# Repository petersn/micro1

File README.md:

## Dependencies:

```
pip install cocotb
sudo apt-get install iverilog
```

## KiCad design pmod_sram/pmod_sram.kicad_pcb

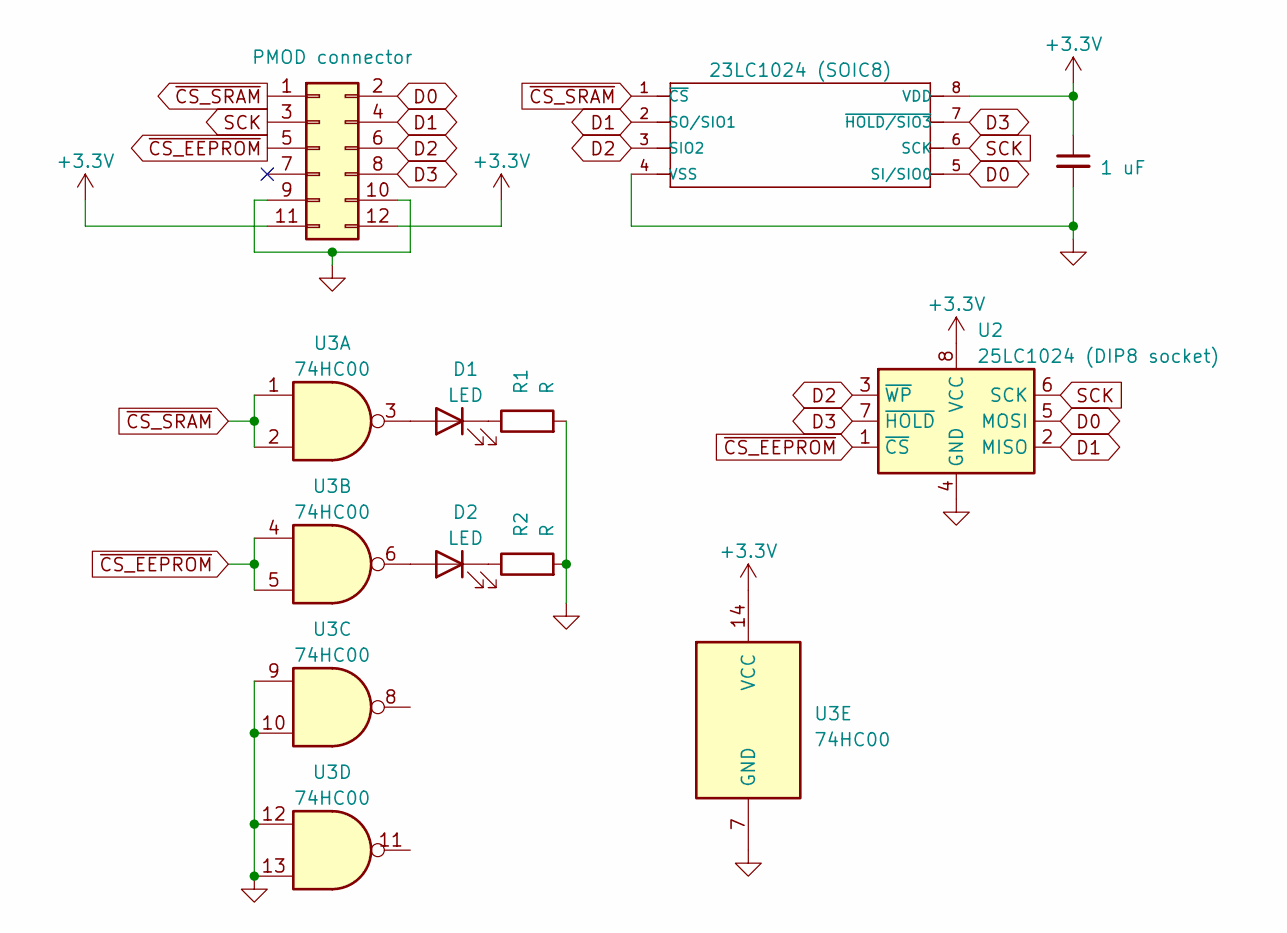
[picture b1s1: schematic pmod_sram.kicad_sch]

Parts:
C1: 1 uF; C_0603_1608Metric_Pad1.08x0.95mm_HandSolder
D1, D2: LED; LED_0603_1608Metric_Pad1.05x0.95mm_HandSolder
J1: PMOD connector; PinHeader_2x06_P2.54mm_Vertical
R1, R2: R; R_0603_1608Metric_Pad0.98x0.95mm_HandSolder
U1: 23LC1024 (SOIC8); SOIC-8_3.9x4.9mm_P1.27mm; MPN 23LC1024T-E/ST
U2: 25LC1024 (DIP8 socket); DIP-8_W7.62mm
U3: 74HC00; SOIC-14_3.9x8.7mm_P1.27mm

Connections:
+3.3V: C1.1, J1.11, J1.12, U1.8 (VDD), U2.8 (VCC), U3.14 (VCC)
D0: J1.2, U1.5 (SI/SIO0), U2.5 (MOSI)
D1: J1.4, U1.2 (SO/SIO1), U2.2 (MISO)
D2: J1.6, U1.3 (SIO2), U2.3 (~WP)
D3: J1.8, U1.7 (~HOLD/SIO3), U2.7 (~HOLD)
GND: C1.2, J1.9, J1.10, R1.2, R2.2, U1.4 (VSS), U2.4 (GND), U3.7 (GND), U3.9, U3.10, U3.12, U3.13
unnamed: D1.2 (A), U3.3
unnamed: D1.1 (K), R1.1
unnamed: D2.2 (A), U3.6
unnamed: D2.1 (K), R2.1
SCK: J1.3, U1.6 (SCK), U2.6 (SCK)
~CS_EEPROM: J1.5, U2.1 (~CS), U3.4, U3.5
~CS_SRAM: J1.1, U1.1 (~CS), U3.1, U3.2

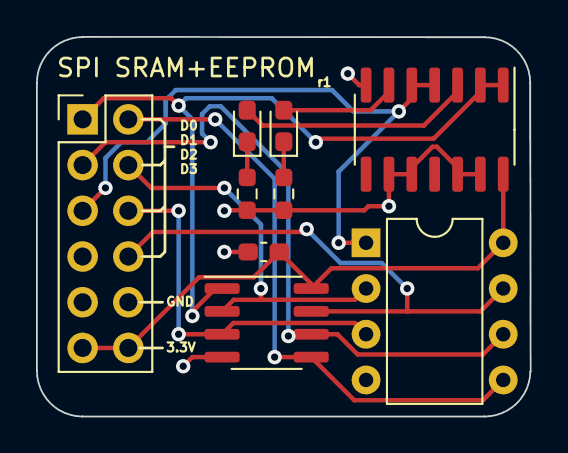
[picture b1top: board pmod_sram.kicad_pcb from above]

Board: 2 copper layers, 27.4 x 21.1 mm, 9 parts (0 on the bottom side), 13 nets.

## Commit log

2023-08-27 Initial experiments
2023-08-27 Add checking for invalid states to the SRAM
2023-08-27 Fix deprecation warning
2023-08-27 Switch to using z as an SRAM output
2023-08-27 Whoops, assignments were backwards
2023-08-27 Tiny changes
2023-08-27 Simple processor
2023-08-27 Whoopsies
2023-08-27 Adding SPI SRAM board r1 that I submitted to pcbway
2023-08-28 More nonsense
2023-11-01 New versions of PCB
2024-04-19 Backup
2024-04-19 Whoops, missed the most important file
2024-04-19 Working random character map
2024-04-19 Simple version, going to try to synthesize this for TT06
2024-04-19 Way more content
2024-04-19 Switching back to big ternary block.
2024-04-19 More changes
2024-04-19 More adjustments to ISA
2024-04-19 Some changes
2024-04-19 Whoops, cache issues
2024-04-19 Whoopsies, now a proper write-through cache
2024-04-19 More edits
2024-04-19 More adjustments
2024-04-19 Shrink font
